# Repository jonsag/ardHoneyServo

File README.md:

# ardHoneyServo
An arduino sketch to run a honey extractor via a servo

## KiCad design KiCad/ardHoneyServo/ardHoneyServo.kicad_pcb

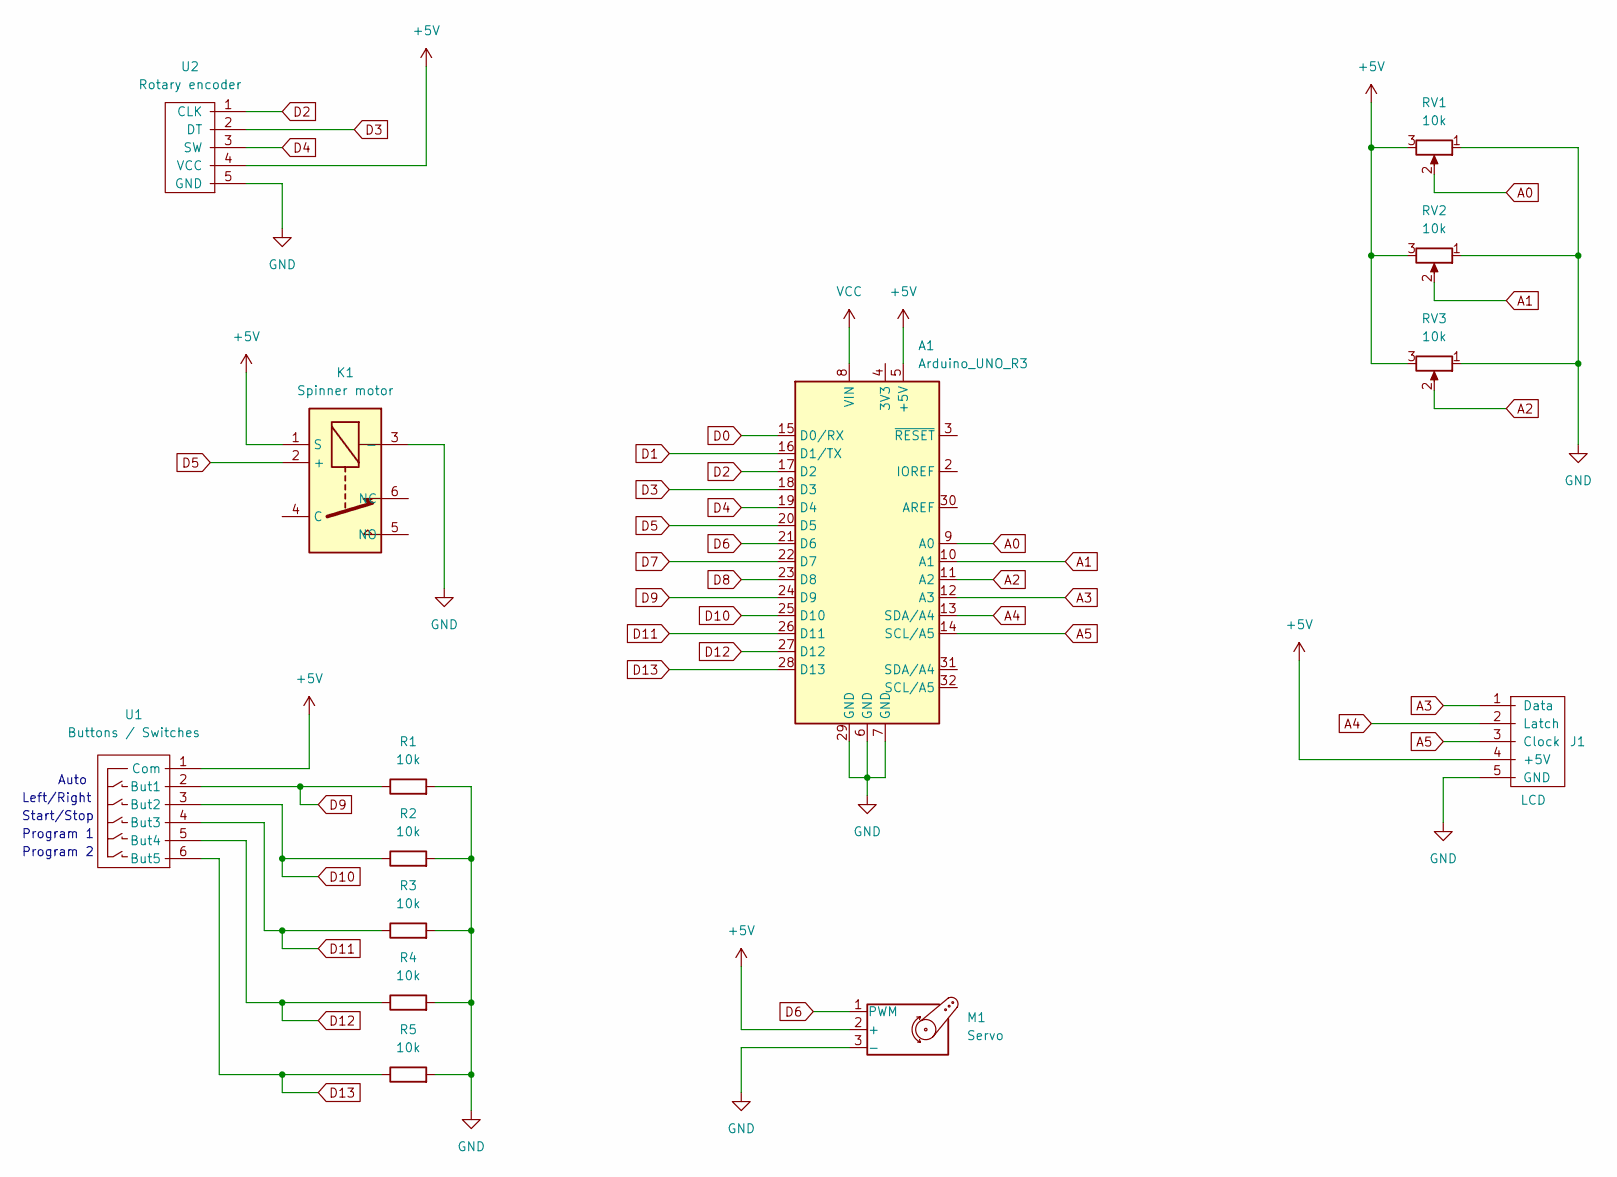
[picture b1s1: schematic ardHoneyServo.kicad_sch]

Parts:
A1: Arduino_UNO_R3; Arduino_UNO_R3_shield_large
J1: LCD; 5-pin JST LCD
K1: Spinner motor; 3-pin JST KY-019 relay
M1: Servo; 3-pin JST Servo
R1, R2, R3, R4, R5: 10k; R_Axial_DIN0207_L6.3mm_D2.5mm_P10.16mm_Horizontal_larger_pa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
RV1, RV2, RV3: 10k; 3-pin JST Potentiometer
U1: Buttons / Switches; 6-pin JST 5-buttons
U2: Rotary encoder; 5-pin JST Rotary Encoder

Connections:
+5V: A1.5 (+5V), J1.4 (+5V), K1.1 (S), M1.2 (+), RV1.3, RV2.3, RV3.3, U1.1 (Com), U2.4 (VCC)
A0: A1.9 (A0), RV1.2
A1: A1.10 (A1), RV2.2
A2: A1.11 (A2), RV3.2
A3: A1.12 (A3), J1.1 (Data)
A4: A1.13 (SDA/A4), J1.2 (Latch)
A5: A1.14 (SCL/A5), J1.3 (Clock)
D0: A1.15 (D0/RX)
D1: A1.16 (D1/TX)
D2: A1.17 (D2), U2.1 (CLK)
D3: A1.18 (D3), U2.2 (DT)
D4: A1.19 (D4), U2.3 (SW)
D5: A1.20 (D5), K1.2 (+)
D6: A1.21 (D6), M1.1 (PWM)
D7: A1.22 (D7)
D8: A1.23 (D8)
D9: A1.24 (D9), R1.1, U1.2 (But1)
D10: A1.25 (D10), R2.1, U1.3 (But2)
D11: A1.26 (D11), R3.1, U1.4 (But3)
D12: A1.27 (D12), R4.1, U1.5 (But4)
D13: A1.28 (D13), R5.1, U1.6 (But5)
GND: A1.6 (GND), A1.7 (GND), A1.29 (GND), J1.5 (GND), K1.3 (-), M1.3 (-), R1.2, R2.2, R3.2, R4.2, R5.2, RV1.1, RV2.1, RV3.1, U2.5 (GND)
VCC: A1.8 (VIN)

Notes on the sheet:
Auto
Start/Stop
Program 2
Left/Right
Program 1

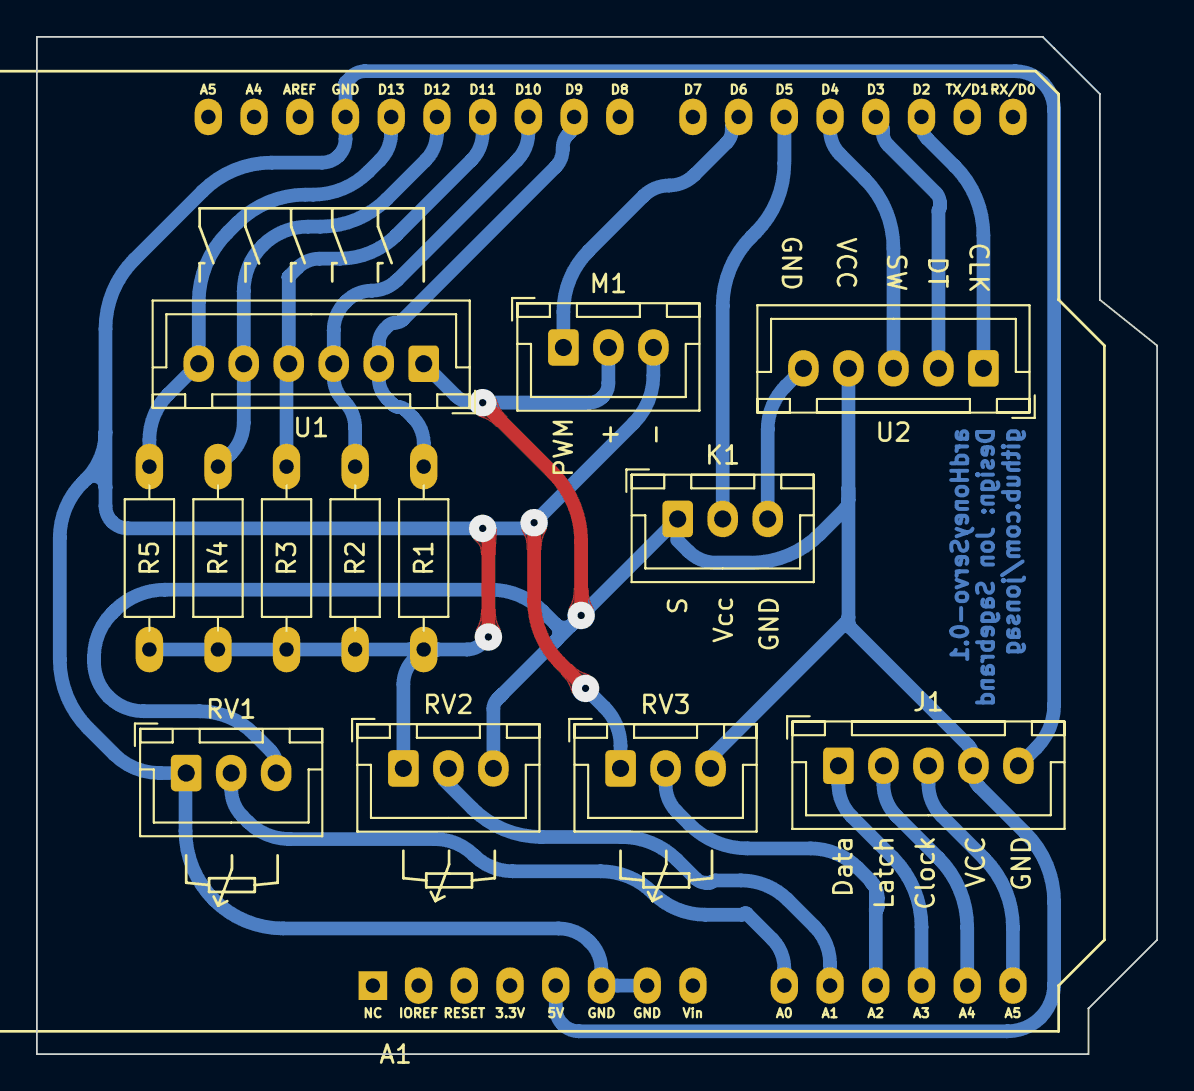
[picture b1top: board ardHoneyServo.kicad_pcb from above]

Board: 2 copper layers, 62.2 x 56.5 mm, 14 parts (0 on the bottom side), 18 nets.

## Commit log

2016-03-06 Commit of example
2016-03-06 Added another example
2016-03-06 First ardHoneyServo
2016-03-07 SOme things working now...
2016-03-09 Last commit before redoing code
2016-03-09 Auto program 1 now working. Also many changes in LCD display
2016-03-10 Now time is set in seconds
2016-03-15 Remove == 1 and == 0
2016-03-19 Revert "Remove == 1 and == 0"
    This reverts commit 8b3adef06ff219969c0ead2fdccb80774ece4b47.
2016-03-19 Now with maxAngle- and zeroOffset-pot
2016-03-25 Now 3 pin LCD
2016-03-26 st colon blinks in program mode 1
2016-03-27 Rotary encoder now wired in
2016-03-27 Now adding to 1-1 percent
2016-03-30 Some changes. Whatever...
2016-03-30 Wrong declaration of variables
2016-04-02 Changed some variable names
2018-11-23 Added Arduino library
2018-11-23 Made connections more clear
2022-09-02 cleaning
2022-09-02 moved to pio, schematics
2023-02-21 kicad7
